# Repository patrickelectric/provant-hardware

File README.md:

provant-hardware
================

#### Descrição ####

Repositório para projeto de Hardware (mecânica e eletrônica) do proVANT. 

#### Estrutura do repositório ####

A pasta _mechanics_ está estruturada em três subpastas:

- __drawings__ : Desenhos técnicos das partes modeladas.
- __images__ :  Renderizações e _prints_ de modelos completos e peças. 
- __models__ : Arquivos dos modelos 3D de partes e montagens.

Os modelos 3D foram desenvolvidos em sua maioria com o uso do CAD [_Solid Works_](www.solidworks.com).

Os esquemáticos e layouts das placas deste projeto foram desenvolvidas com software de EDA [_Eagle_](www.cadsoftusa.com/), e estão contidos na pasta _electronics_. Esta está estruturada em:

- __lib__ :  Contem bibliotecas de componentes exclusivos do projeto, bem como bibliotecas de terceiros (não padrões no Eagle) que foram utilizadas.
- __stm32-e407-shield__ : Contem esquemático/layout do shield desenvolvido para a placa __antiga__ utilizada no projeto, a [STM32-H407](https://www.olimex.com/Products/ARM/ST/STM32-H407/open-source-hardware). Esta pasta e seus conteúdos podem ser considerados __obsoletos__ .
- __stm32f4discovery-shield__ : Contem o esquemático/layout da placa breakout sendo utilizada atualmente no projeto, projetada para a [STM32F4-Discovery](http://www.st.com/web/catalog/tools/FM116/SC959/SS1532/PF252419?sc=internet/evalboard/product/252419.jsp).

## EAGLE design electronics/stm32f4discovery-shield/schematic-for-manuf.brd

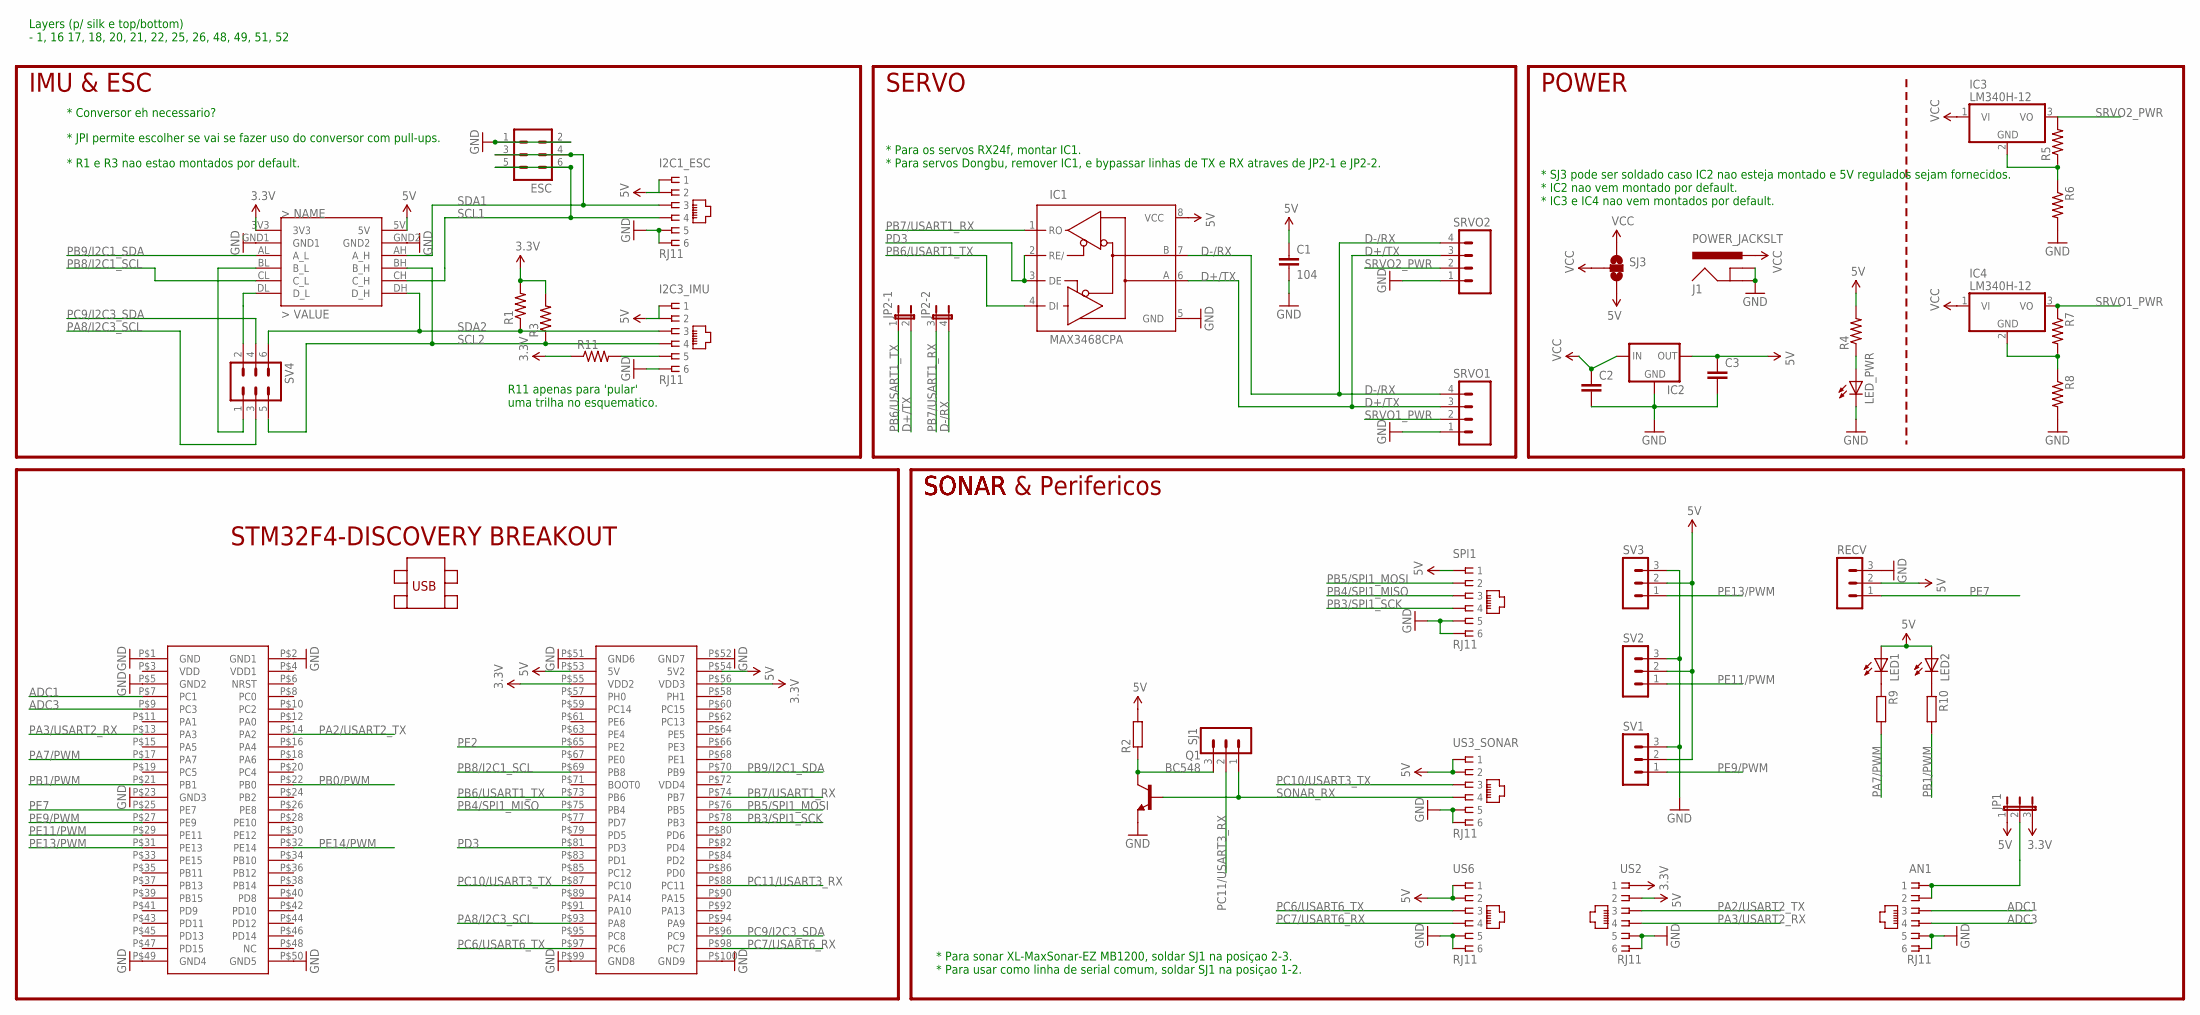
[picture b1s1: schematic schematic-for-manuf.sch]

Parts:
AN1: RJ11; RJ12-PROVANT
C1: 104; CAP-PTH-SMALL-KIT
C2: C7.5/3; C7.5B3
C3: 0.1UF-50V-20%(PTH)KIT-EZ; CAP-PTH-SMALL-KIT
ESC: MA03-2
I2C1_ESC, I2C3_IMU: RJ11; RJ12-PROVANT
IC1: MAX3468CPA; DIL08
IC2: V_REG_78XX-TO-220; TO-220-ALT
IC3, IC4: LM340H-12; TO220H
J1: POWER_JACKSLT; POWER_JACK_SLOT
JP1: JP2E; JP2
JP2: JP2QE; JP2Q
LED1, LED2: LED3MM
LED_PWR: LED5MM
Q1: BC548; TO92-EBC
R1, R3: R-US_0204/5; 0204/5
R2: R-EU_0204/7; 0204/7
R4, R5, R6, R7, R8: R-US_0204/7; 0204/7
R9, R10: R-EU_0204/2V; 0204V
R11: R-US_M1406; M1406
RECV: MA03-1
SJ1: MA03-1
SJ3: SOLDERJUMPER_2WAY-OLDW; SJ_2W
SPI1: RJ11; RJ12-PROVANT
SRVO1, SRVO2: M04POLAR; MOLEX-1X4
SV1, SV2, SV3: MA03-1
SV4: MA03-2
U$1: STM32F4-DISCOVERY
U$2: JYMCU_LOGIC_LEVEL_CONVERTER; JYMCU_LOGIC_LEVEL_SHIFTER_DIP
US2, US3_SONAR, US6: RJ11; RJ12-PROVANT

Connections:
3.3V: JP1.3, R1.2, R3.2, R11.1, U$1.P$55 (VDD2), U$1.P$56 (VDD3), U$2.3V3, US2.P1 (1)
5V: C1.1, C3.1, I2C1_ESC.P1 (1), I2C1_ESC.P2 (2), I2C3_IMU.P1 (1), I2C3_IMU.P2 (2), IC1.8 (VCC), IC2.OUT, JP1.1, LED1.A, LED2.A, R2.2, R4.2, RECV.2, SJ3.3, SPI1.P1 (1), SV1.2, SV2.2, SV3.2, U$1.P$53 (5V), U$1.P$54 (5V2), U$2.5V, US2.P2 (2), US3_SONAR.P1 (1), US3_SONAR.P2 (2), US6.P1 (1), US6.P2 (2)
ADC1: AN1.P3 (3), U$1.P$7 (PC1)
ADC3: AN1.P4 (4), U$1.P$9 (PC3)
D+/TX: IC1.6 (A), JP2.2, SRVO1.3, SRVO2.3
D-/RX: IC1.7 (B), JP2.4 (2), SRVO1.4, SRVO2.4
GND: AN1.P5 (5), AN1.P6 (6), C1.2, C2.2, C3.2, ESC.1, ESC.2, I2C1_ESC.P5 (5), I2C1_ESC.P6 (6), I2C3_IMU.P6 (6), IC1.5 (GND), IC2.GND, J1.GND@1 (GNDBREAK), J1.GND@2 (GND), LED_PWR.K (C), Q1.E, R6.2, R8.2, RECV.3, SPI1.P5 (5), SPI1.P6 (6), SRVO1.1, SRVO2.1, SV1.3, SV2.3, SV3.3, U$1.P$1 (GND), U$1.P$2 (GND1), U$1.P$5 (GND2), U$1.P$23 (GND3), U$1.P$49 (GND4), U$1.P$50 (GND5), U$1.P$51 (GND6), U$1.P$52 (GND7), U$1.P$99 (GND8), U$1.P$100 (GND9), U$2.GND1, U$2.GND2, US2.P5 (5), US2.P6 (6), US3_SONAR.P5 (5), US3_SONAR.P6 (6), US6.P5 (5), US6.P6 (6)
unnamed: SV4.2, U$2.DL (D_L)
unnamed: SV4.1, U$2.BL (B_L)
unnamed: Q1.C, R2.1, SJ1.3
unnamed: LED_PWR.A, R4.1
unnamed: LED1.K (C), R9.1
unnamed: IC3.2 (GND), R5.1, R6.1
unnamed: LED2.K (C), R10.1
unnamed: IC4.2 (GND), R7.2, R8.1
unnamed: I2C3_IMU.P5 (5), R11.2
unnamed: AN1.P1 (1), AN1.P2 (2), JP1.2
PA2/USART2_TX: U$1.P$14 (PA2), US2.P3 (3)
PA3/USART2_RX: U$1.P$13 (PA3), US2.P4 (4)
PA7/PWM: R9.2, U$1.P$17 (PA7)
PA8/I2C3_SCL: SV4.3, U$1.P$93 (PA8)
PB0/PWM: U$1.P$22 (PB0)
PB1/PWM: R10.2, U$1.P$21 (PB1)
PB3/SPI1_SCK: SPI1.P4 (4), U$1.P$78 (PB3)
PB4/SPI1_MISO: SPI1.P3 (3), U$1.P$75 (PB4)
PB5/SPI1_MOSI: SPI1.P2 (2), U$1.P$76 (PB5)
PB6/USART1_TX: IC1.4 (DI), JP2.1, U$1.P$73 (PB6)
PB7/USART1_RX: IC1.1 (RO), JP2.3 (1), U$1.P$74 (PB7)
PB8/I2C1_SCL: U$1.P$69 (PB8), U$2.CL (C_L)
PB9/I2C1_SDA: U$1.P$70 (PB9), U$2.AL (A_L)
PC6/USART6_TX: U$1.P$97 (PC6), US6.P3 (3)
PC7/USART6_RX: U$1.P$98 (PC7), US6.P4 (4)
PC9/I2C3_SDA: SV4.4, U$1.P$96 (PC9)
PC10/USART3_TX: U$1.P$87 (PC10), US3_SONAR.P3 (3)
PC11/USART3_RX: SJ1.2, U$1.P$88 (PC11)
PD3: IC1.2 (RE/), IC1.3 (DE), U$1.P$81 (PD3)
PE2: U$1.P$65 (PE2)
PE7: RECV.1, U$1.P$25 (PE7)
PE9/PWM: SV1.1, U$1.P$27 (PE9)
PE11/PWM: SV2.1, U$1.P$29 (PE11)
PE13/PWM: SV3.1, U$1.P$31 (PE13)
PE14/PWM: U$1.P$32 (PE14)
SCL1: ESC.5, ESC.6, I2C1_ESC.P4 (4), U$2.CH (C_H)
SCL2: I2C3_IMU.P4 (4), R3.1, SV4.5, U$2.BH (B_H)
SDA1: ESC.3, ESC.4, I2C1_ESC.P3 (3), U$2.AH (A_H)
SDA2: I2C3_IMU.P3 (3), R1.1, SV4.6, U$2.DH (D_H)
SONAR_RX: Q1.B, SJ1.1, US3_SONAR.P4 (4)
SRVO1_PWR: IC4.3 (VO), R7.1, SRVO1.2
SRVO2_PWR: IC3.3 (VO), R5.2, SRVO2.2
VCC: C2.1, IC2.IN, IC3.1 (VI), IC4.1 (VI), J1.PWR, SJ3.1, SJ3.2

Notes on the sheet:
IMU & ESC
SERVO
* Conversor eh necessario?
* JPI permite escolher se vai se fazer uso do conversor com pull-ups.
* R1 e R3 nao estao montados por default.
POWER
* SJ3 pode ser soldado caso IC2 nao esteja montado e 5V regulados sejam fornecidos. * IC2 nao vem montado por default. * IC3 e IC4 nao vem montados por default.
* Para os servos RX24f, montar IC1. * Para servos Dongbu, remover IC1, e bypassar linhas de TX e RX atraves de JP2-1 e JP2-2.
* Para sonar XL-MaxSonar-EZ MB1200, soldar SJ1 na posiçao 2-3. * Para usar como linha de serial comum, soldar SJ1 na posiçao 1-2.
SONAR
SONAR & Perifericos
Layers (p/ silk e top/bottom) - 1, 16 17, 18, 20, 21, 22, 25, 26, 48, 49, 51, 52
R11 apenas para 'pular' uma trilha no esquematico.

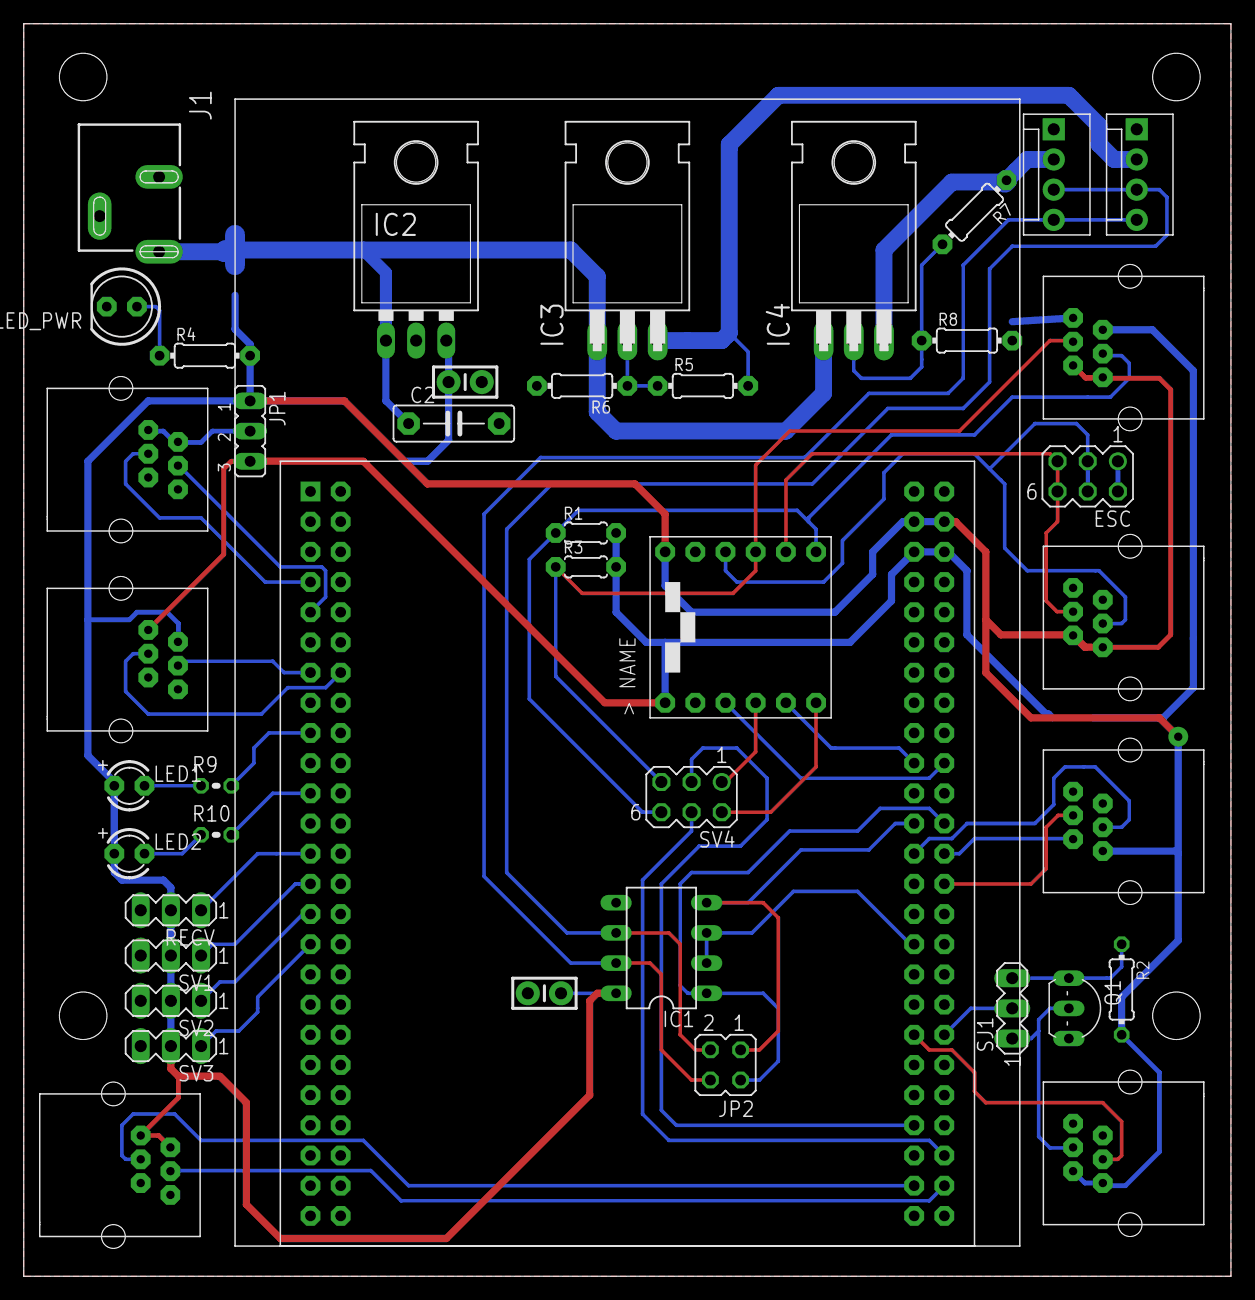
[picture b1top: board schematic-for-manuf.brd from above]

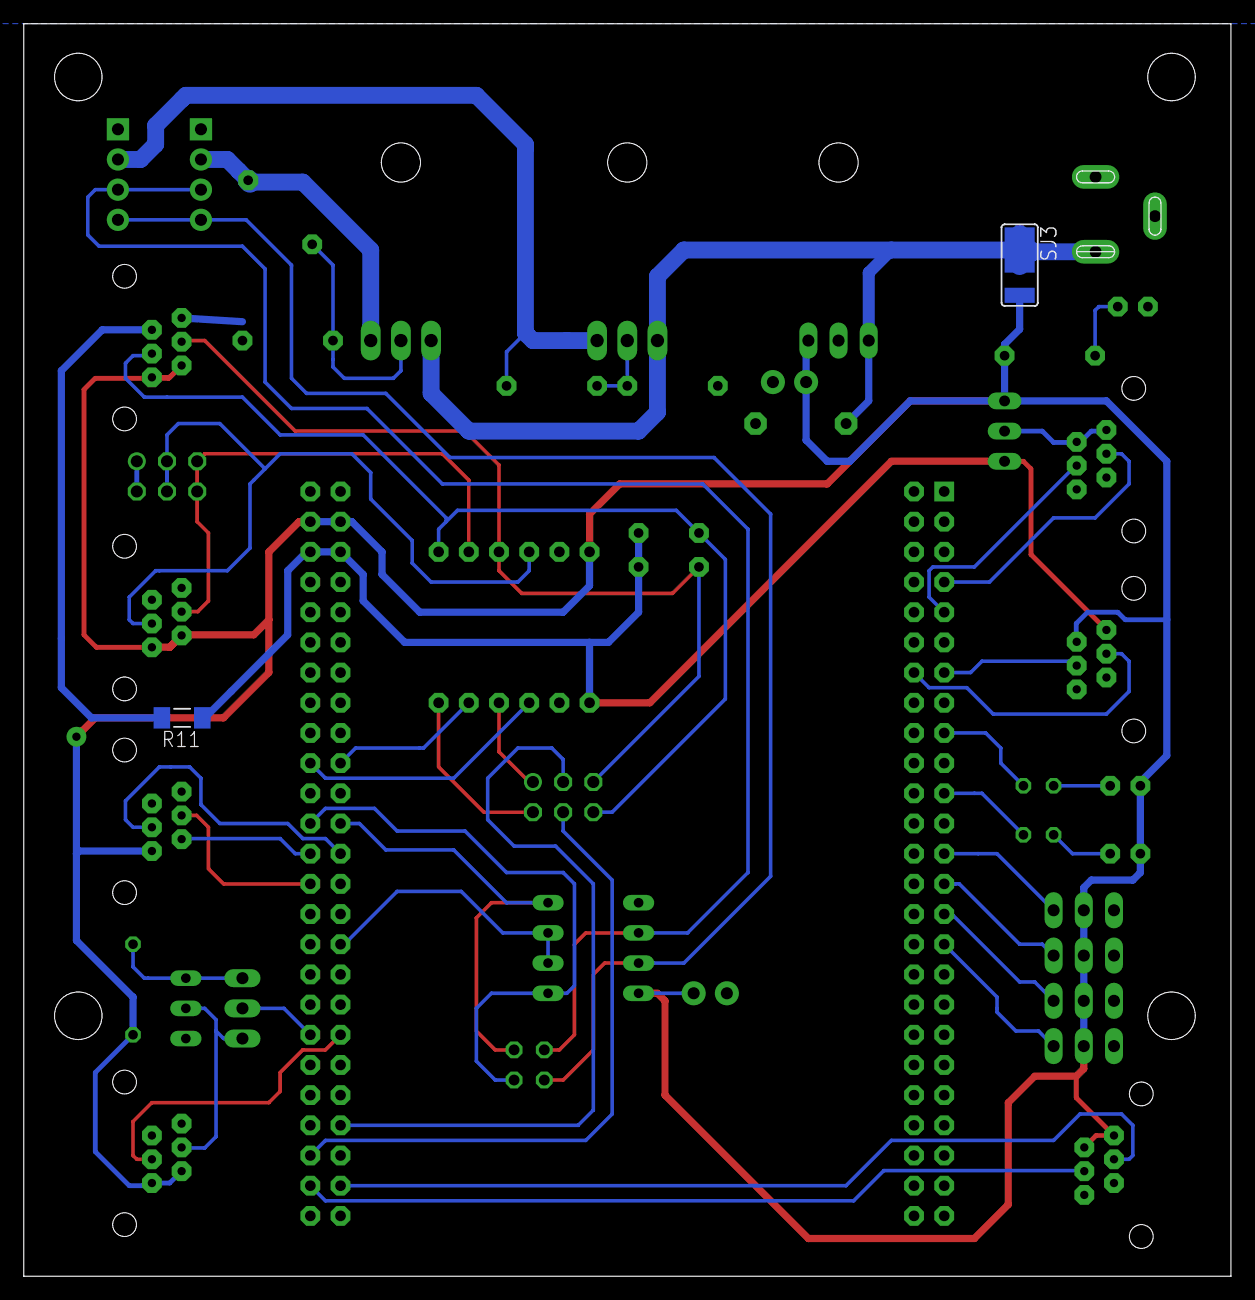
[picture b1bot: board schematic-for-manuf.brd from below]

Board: 2 copper layers, 101.6 x 105.4 mm, 44 parts (2 on the bottom side), 47 nets.

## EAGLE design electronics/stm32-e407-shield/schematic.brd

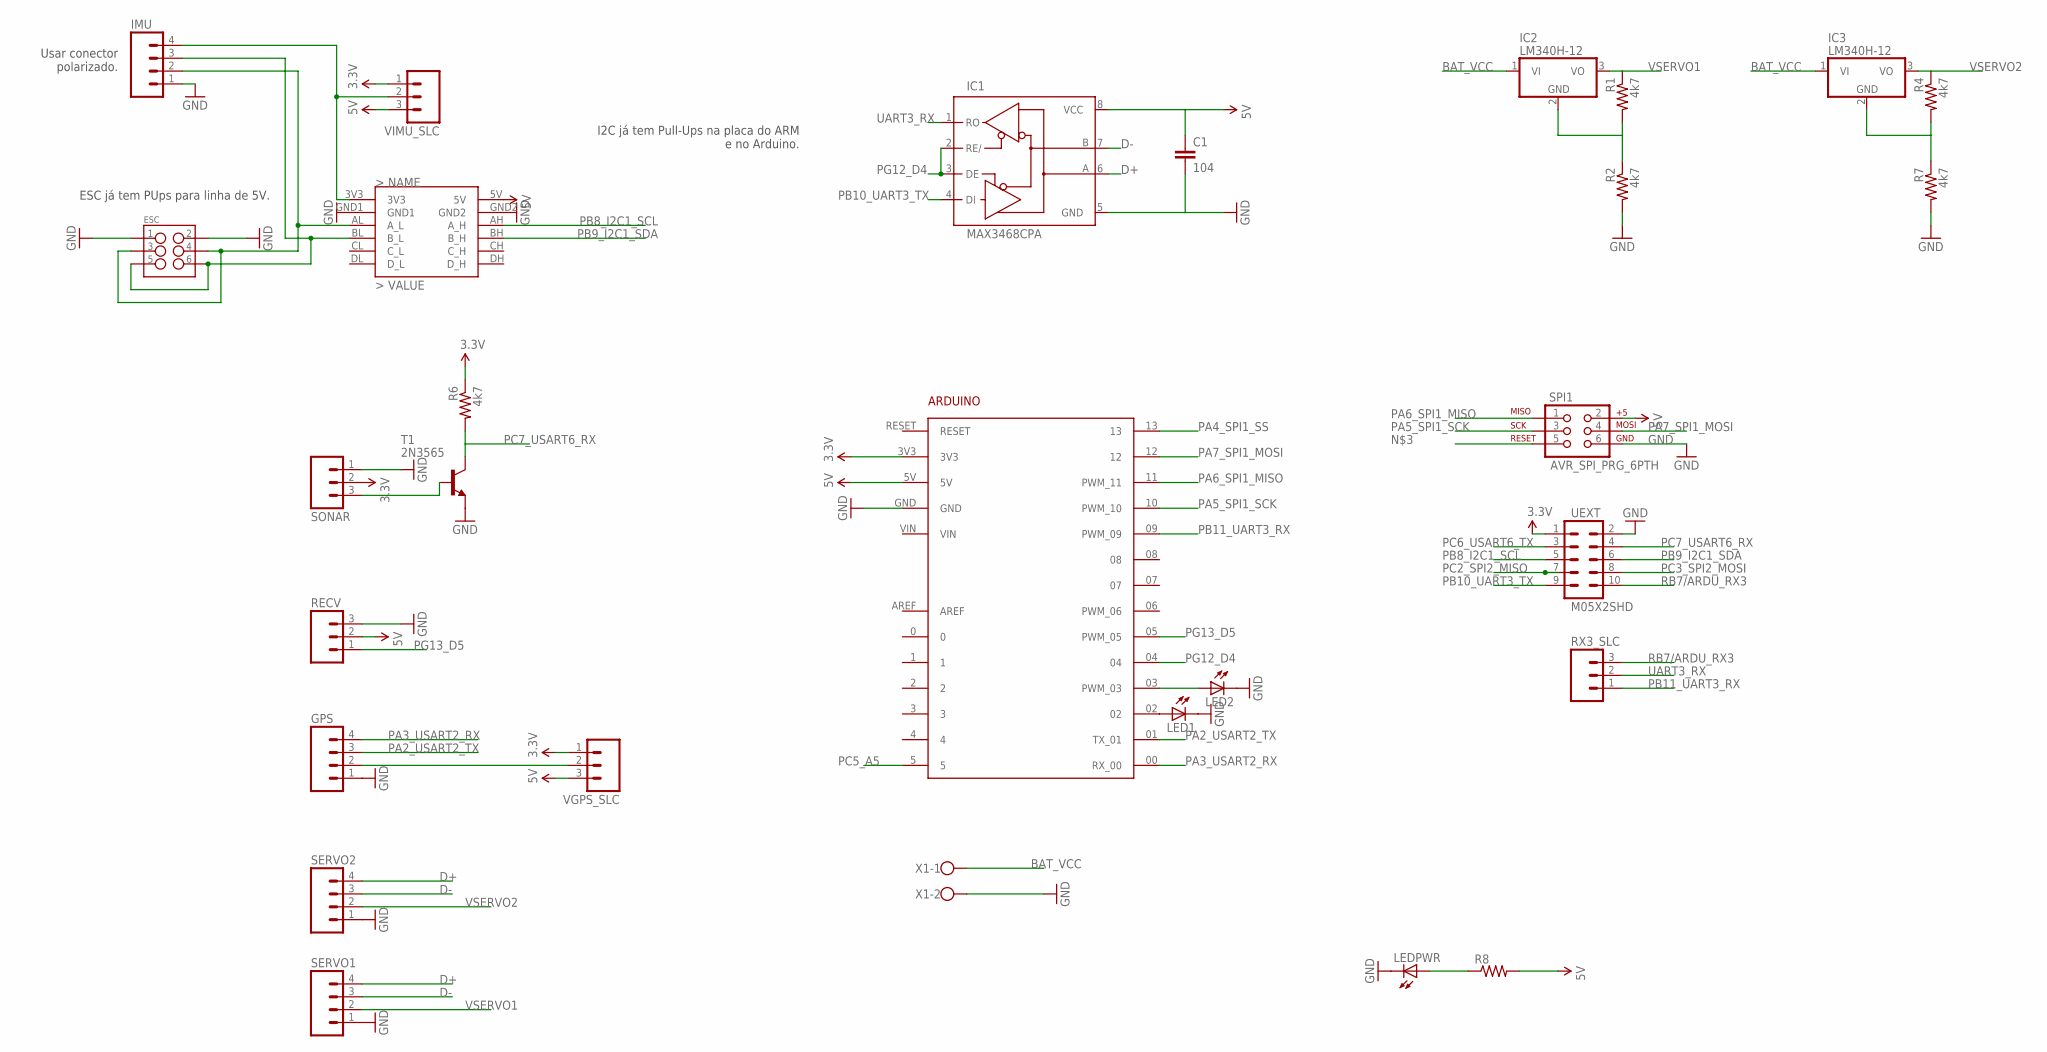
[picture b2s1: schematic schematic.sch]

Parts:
ARDUINO1: ARDUINO
C1: 104; CAP-PTH-SMALL-KIT
ESC: M03X22X3_SILK_SM; 2X3
GPS: M04PTH; 1X04
IC1: MAX3468CPA; DIL08
IC2, IC3: LM340H-12; TO220H
IMU: M04PTH; 1X04
LED1, LED2: LED3MM
LEDPWR: LED3MM
R1, R4: 4k7; 0309V
R2, R7: 4k7; 0204/7
R6: 4k7; M1406
R8: RESISTORPTH-1/6W; 1/6W-RES
RECV: M03PTH; 1X03
RX3_SLC: M03PTH; 1X03
SERVO1, SERVO2: M04PTH; 1X04
SONAR: M03PTH; 1X03
SPI1: AVR_SPI_PRG_6PTH; 2X3
T1: 2N3565; TO92
U$1: JYMCU_LOGIC_LEVEL_CONVERTER; JYMCU_LOGIC_LEVEL_SHIFTER_DIP
UEXT: M05X2SHD; 2X5-SHROUDED
VGPS_SLC: M03PTH; 1X03
VIMU_SLC: M03PTH; 1X03
X1: W237-102

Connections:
3.3V: ARDUINO1.3V3, R6.1, SONAR.2, UEXT.1, VGPS_SLC.1, VIMU_SLC.1
5V: ARDUINO1.5V, C1.1, IC1.8 (VCC), R8.2, RECV.2, SPI1.2, U$1.5V, VGPS_SLC.3, VIMU_SLC.3
BAT_VCC: IC2.1 (VI), IC3.1 (VI), X1.1
D+: IC1.6 (A), SERVO1.4, SERVO2.4
D-: IC1.7 (B), SERVO1.3, SERVO2.3
GND: ARDUINO1.GND, C1.2, ESC.1, ESC.2, GPS.1, IC1.5 (GND), IMU.1, LED1.K (C), LED2.K (C), LEDPWR.K (C), R2.2, R7.2, RECV.3, SERVO1.1, SERVO2.1, SONAR.1, SPI1.6, T1.3 (E), U$1.GND1, U$1.GND2, UEXT.2, X1.2
unnamed: IMU.4, U$1.3V3, VIMU_SLC.2
unnamed: SONAR.3, T1.2 (B)
unnamed: ESC.3, ESC.4, IMU.2, U$1.AL (A_L)
unnamed: GPS.2, VGPS_SLC.2
unnamed: ARDUINO1.02, LED1.A
unnamed: ARDUINO1.03 (PWM_03), LED2.A
unnamed: LEDPWR.A, R8.1
unnamed: ESC.5, ESC.6, IMU.3, U$1.BL (B_L)
unnamed: IC3.2 (GND), R4.2, R7.1
unnamed: IC2.2 (GND), R1.2, R2.1
PA2_USART2_TX: ARDUINO1.01 (TX_01), GPS.3
PA3_USART2_RX: ARDUINO1.00 (RX_00), GPS.4
PA4_SPI1_SS: ARDUINO1.13
PA5_SPI1_SCK: ARDUINO1.10 (PWM_10), SPI1.3
PA6_SPI1_MISO: ARDUINO1.11 (PWM_11), SPI1.1
PA7_SPI1_MOSI: ARDUINO1.12, SPI1.4
PB8_I2C1_SCL: U$1.AH (A_H), UEXT.5
PB9_I2C1_SDA: U$1.BH (B_H), UEXT.6
PB10_UART3_TX: IC1.4 (DI), UEXT.9
PB11_UART3_RX: ARDUINO1.09 (PWM_09), RX3_SLC.1
PC2_SPI2_MISO: UEXT.7
PC3_SPI2_MOSI: UEXT.8
PC5_A5: ARDUINO1.5
PC6_USART6_TX: UEXT.3
PC7_USART6_RX: R6.2, T1.1 (C), UEXT.4
PG12_D4: ARDUINO1.04, IC1.2 (RE/), IC1.3 (DE)
PG13_D5: ARDUINO1.05 (PWM_05), RECV.1
RB7/ARDU_RX3: RX3_SLC.3, UEXT.10
UART3_RX: IC1.1 (RO), RX3_SLC.2
VSERVO1: IC2.3 (VO), R1.1, SERVO1.2
VSERVO2: IC3.3 (VO), R4.1, SERVO2.2

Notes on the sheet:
I2C já tem Pull-Ups na placa do ARM e no Arduino.
ESC já tem PUps para linha de 5V.
Usar conector polarizado.

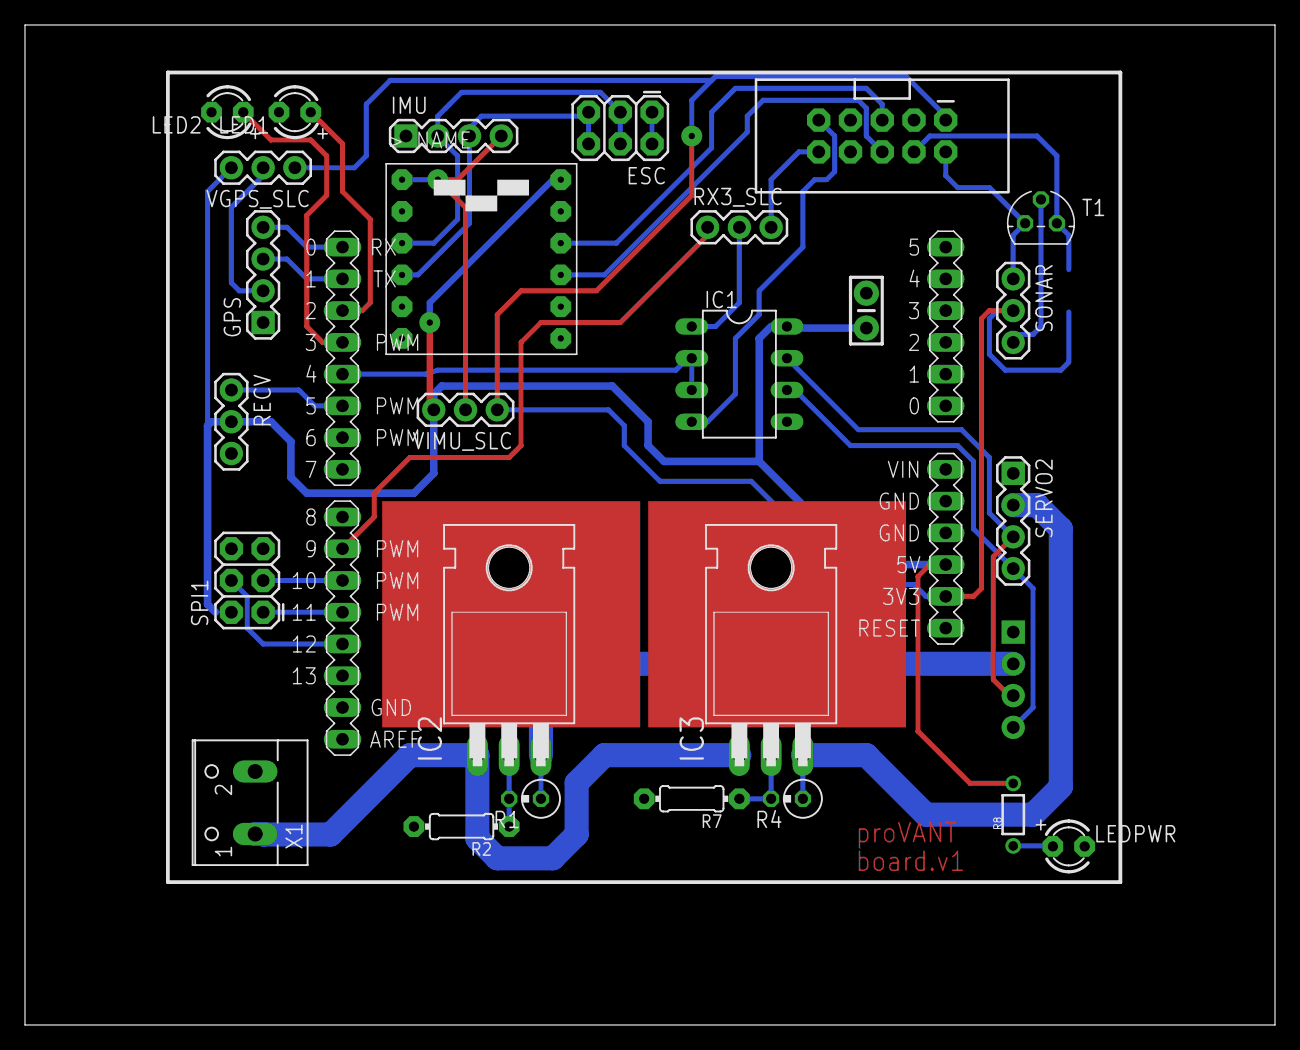
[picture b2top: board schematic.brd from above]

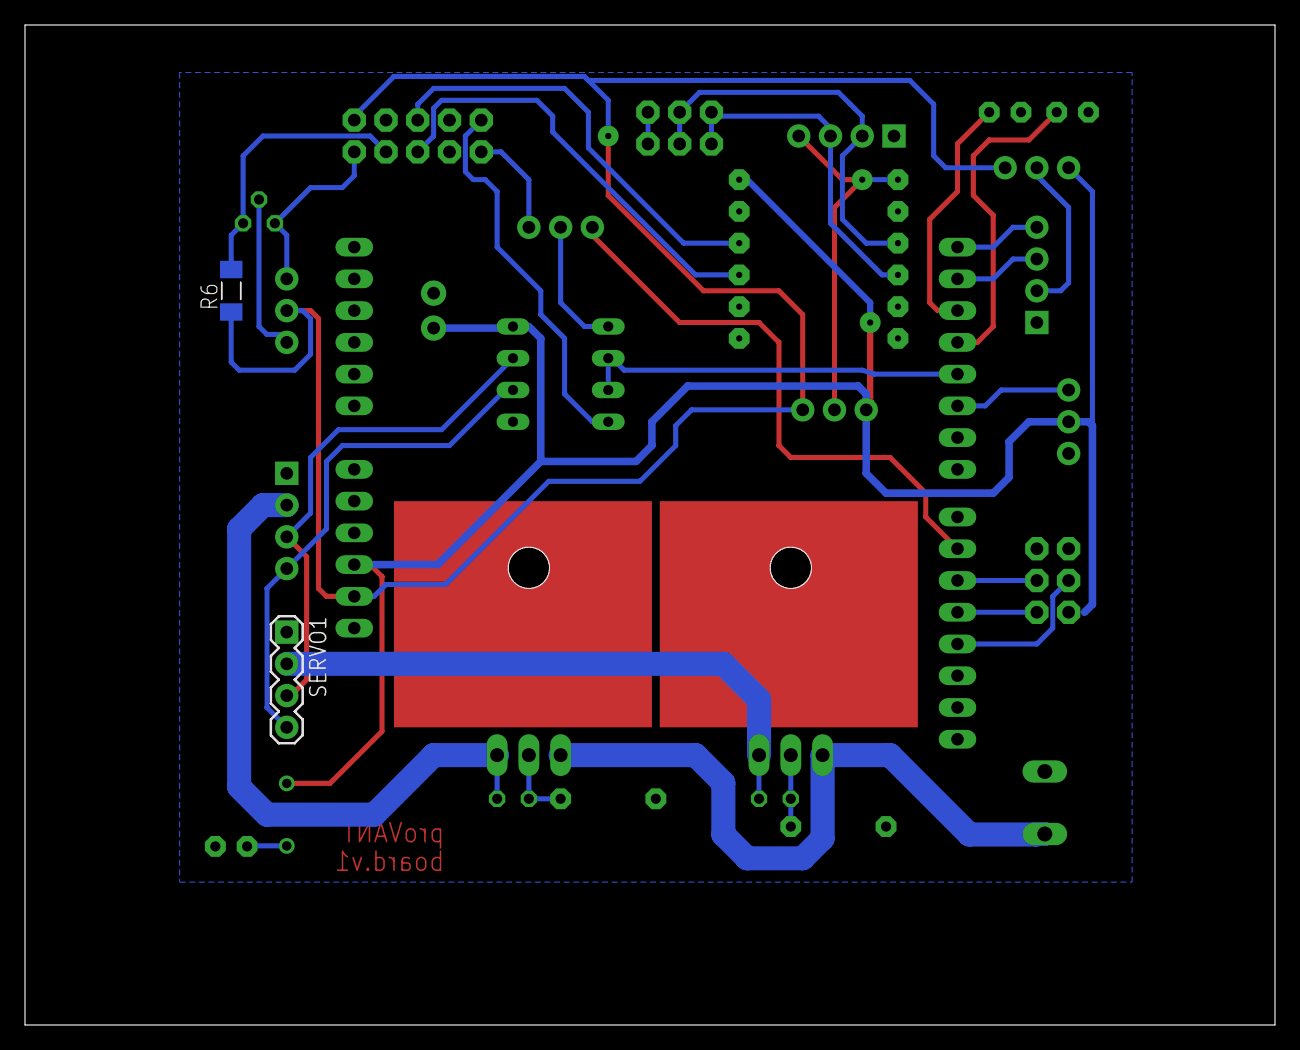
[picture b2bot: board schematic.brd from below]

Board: 2 copper layers, 100.0 x 80.0 mm, 29 parts (2 on the bottom side), 32 nets.

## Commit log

2014-01-22 Adição dos primeiros arquivos.
    Colocados arquivos base do repositório de mecânica e eletrônica.
    As versões ainda não são finais ou estáveis - um tag será liberado
    na primeira versão funcional dos arquivos.
2014-01-29 Alterações no Shield para ARM e biblioteca padrão.
    O conversor lógico foi modelado no Eagle e adicionado à recem criada
    biblioteca provant_custom.lbr. Ele foi então usado para substituir
    o coversor lógico hard-core que havia sido previamente projetado.
    Planos para remover o IMU_SLC - ele agora influencia a tensão do
    barramento do ESC, o que não é desejado.
    new file: .gitignore
2014-02-04 Versão dual layer pra fabricação manual.
2014-02-04 Criados os arquivos para fresa.
    Adicionados um layout e esquemático para fabricação dual layer em fresa.
    Trilhas foram espaçadas algumas foram passadas de bottom para top.
    R6 passou a ser through-hole. Pinos de terra foram identificados com
    uma anotação 'GND' no layer 48 (Document) uma vez que fresa não consegue
    trabalhar diretamente com o groud plane gerado pelo Eagle.
    new file: stm32-e407-shield/schematic-cnc.brd
2014-02-13 Pequenas correções depois da primeira tentativa de fabricação.
2014-02-24 Inicio do projeto do Shield para STM32F4-Discovery.
2014-02-24 Adicionando arquivos do novo shield.
2014-02-25 Iniciando o routing.
2014-02-27 Primeira versao para fabricacao da placa STM32 Discovery.
2014-03-01 Adicionadas algumas correcoes.
2014-03-11 Alterados os pads do componente da STM32F4-Discovery (pads octogonais, 0.066 com o menor drill). Conectores alterados para serem compatíveis com plugs RJ11 (usando principalmente as 4 vias do centro).
2014-03-11 Iniciando revisao da shield Discovery.
2014-03-17 Alterado o layout da placa, removidas algumas frescuras.
2014-03-20 Adicionado o jack para sensores analógicos. LEDs trocados para LEDs de 3mm. Verificaçao de routing do GND feita - aparentemente, sem problemas.
2014-03-29 Realizado o roteamento Dual-Layer para fresamento.
    Aumento de espacamento (trilhas de 24mil, espacamento 24mil)
2014-03-31 Small fixes.
2014-05-04 Corrigido o conversor logico invertido e a pinagem incorreta de algumas portas.
2014-05-06 Atualizada imagem da placa.
2014-05-23 modified: electronics/stm32f4discovery-shield/schematic.brd
2014-05-23 Mounting holes na placa.
2014-07-23 Correcoes finais a placa.
    - Conectores RECV, SV1, SV2 e SV3 movidos mais para a borda da placa.
    - 5V disponiveis no pino 2 do conector US6.
    - Conector US5_SONAR renomeado para US3_SONAR (por usar a USART3)
    - No conector I2C3_IMU, GND disponivel agora no pino 2 e 3v3 no pino 1.
    - Pino de GND do MAX485 ok (antes desconectado da malha de terra).
    - GND disponivel nos pinos 5 e 6 do conector US3_SONAR.
2014-08-04 Atualizado README.md com breve descricao do repositorio.
2014-08-14 Adicao dos sch/brd para o pedido de fabricacao.
    Esses arquivos deverao ser editados para atenderem as requiscoes do fabricante (toleracias, tamanhos) e serao utilzados para gerar os Gerbers de fabricacao.
    new file: schematic-for-manuf.brd
    new file: schematic-for-manuf.sch
2014-08-18 Algumas alteracoes, adicao de anotacoes.
2014-09-06 new file: .gitignore modified: electronics/stm32f4discovery-shield/anotacoes_para_manufatura.txt modified: electronics/stm32f4discovery-shield/schematic-for-manuf.brd
2014-09-09 Routing principal completo.
2014-09-12 Introduzido jumper para servo Dongbu.
2014-09-15 Adicionados gerbers de fabricacao.
    - Adicionados configuracao de CAM para o Eagle
    - Adicionado tutorial de geracao de Gerbers
    - Imagens renderizadas da placa (a partir dos gerbers)
2014-09-16 Atualizando tamanho do drill do logic-shifter.
2014-09-16 Correcao dos gerbers (Windows gerou o silk errado, no Mac ficou OK)
2014-09-16 Adicionando printscreens da renderizacao dos novos gerbers.
2014-10-14 Adicionando manual de uso do shield.
2015-01-21 adicionado conectores para o gps
2015-01-22 adicionado nota do numero 1 na placa para facilitar montagem
2015-07-22 atualizando computador
2015-10-20 adicionando readme do GPS assim como a documentacao da placa para fazer a adaptacao das mensagens do GPS->VANT
2015-10-20 modificando readme
2015-10-20 modificando readme para para corringir problemas de interpretacao do github
2015-10-20 arrumando erros de portugues
2016-01-19 Adicionando ultima documentação
2019-01-21 [ImgBot] Optimize images
    *Total -- 5,069.53kb -> 4,223.17kb (16.69%)
    /electronics/stm32f4discovery-shield/board.png -- 111.81kb -> 49.65kb (55.6%)
    /electronics/stm32f4discovery-shield/schematic.png -- 183.56kb -> 124.65kb (32.09%)
    /mechanics/images/ducted fan_novo_corte.JPG -- 41.33kb -> 28.68kb (30.61%)
    /electronics/stm32f4discovery-shield/gerber/placa_renderizada_bottom.png -- 579.92kb -> 415.00kb (28.44%)
    /electronics/stm32f4discovery-shield/gerber/placa_renderizada_top.png -- 639.13kb -> 463.84kb (27.43%)

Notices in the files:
parts and their libraries:
SparkFun-Connectors: Licensing: CC v3.0 Share-Alike You are welcome to use this library for commercial purposes.
